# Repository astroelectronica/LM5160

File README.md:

# LM5160
Wide Input 65-V, 2-A Synchronous Buck / Fly-Buck DC/DC Converter

https://www.ti.com/product/LM5160

AE01007160

----

Small Footprint Isolated DC/DC Converter for Analog Input Module Reference Design

https://www.ti.com/tool/TIDA-00689

TIDA-00689

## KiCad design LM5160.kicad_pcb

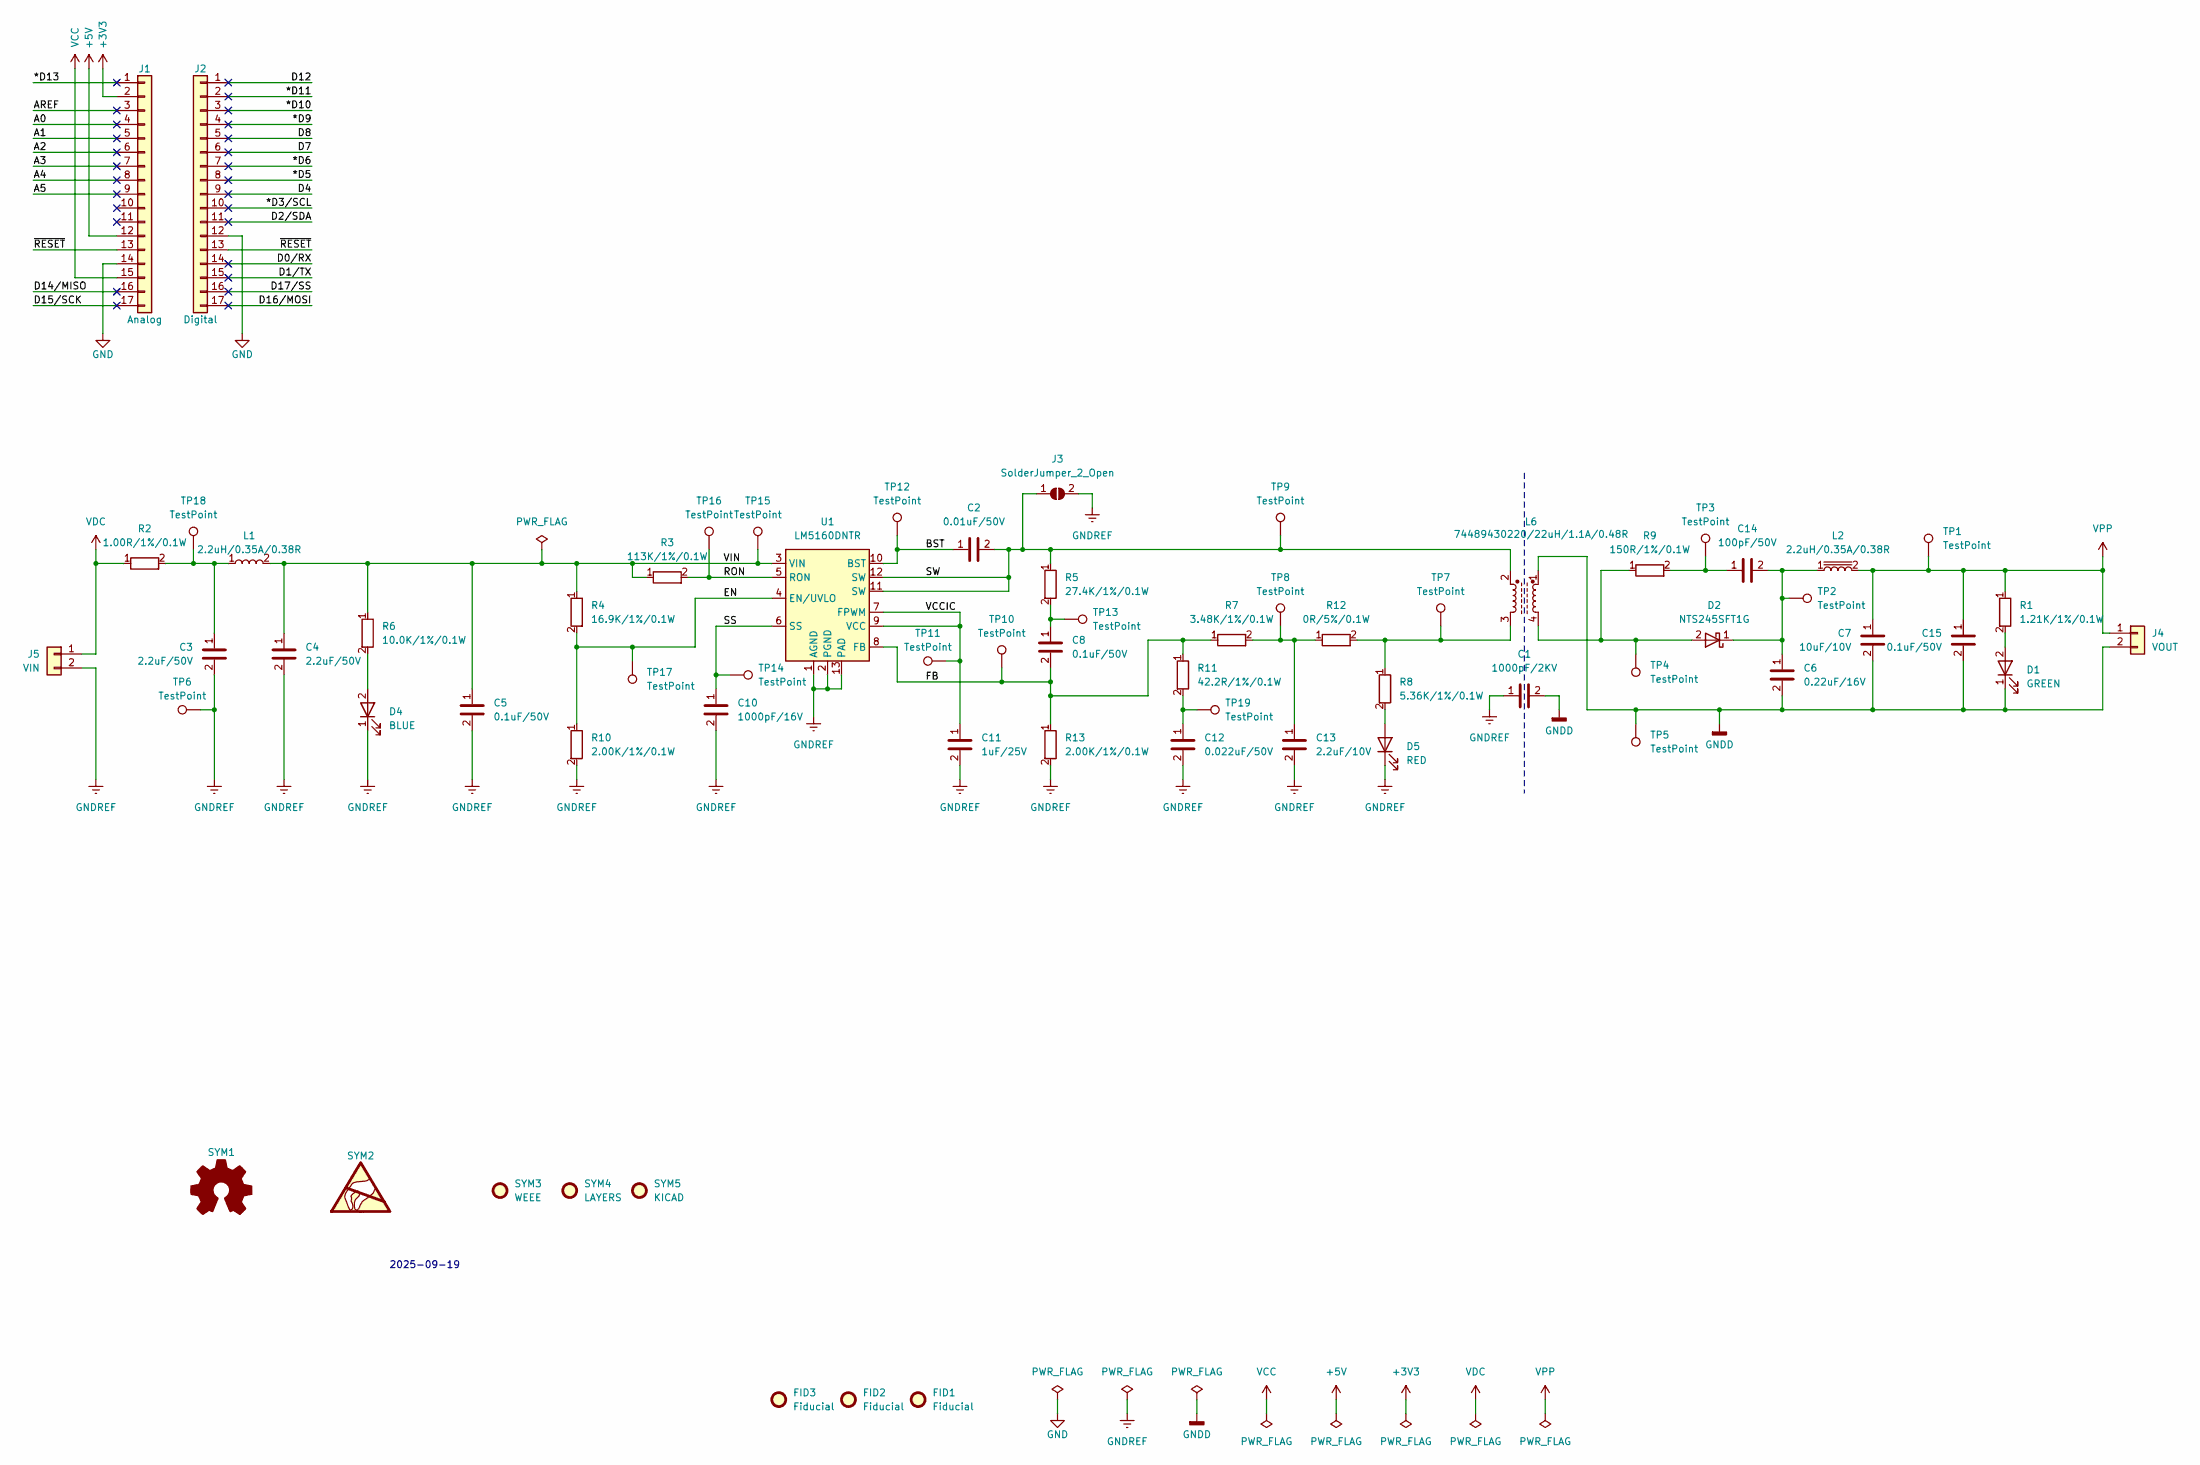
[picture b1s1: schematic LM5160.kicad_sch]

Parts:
C1: 1000pF/2KV; C_1206_3216Metric
C2: 0.01uF/50V; C_0603_1608Metric
C3, C4: 2.2uF/50V; C_1206_3216Metric
C5, C8, C15: 0.1uF/50V; C_0603_1608Metric
C6: 0.22uF/16V; C_0603_1608Metric
C7: 10uF/10V; C_0805_2012Metric
C10: 1000pF/16V; C_0603_1608Metric
C11: 1uF/25V; C_0603_1608Metric
C12: 0.022uF/50V; C_0603_1608Metric
C13: 2.2uF/10V; C_0603_1608Metric
C14: 100pF/50V; C_0603_1608Metric
D1: GREEN; LED_0603_1608Metric
D2: NTS245SFT1G; D_SOD-123F
D4: BLUE; LED_0603_1608Metric
D5: RED; LED_0603_1608Metric
FID1, FID2, FID3: Fiducial; Fiducial_0.75mm_Mask2.25mm
J1: Analog; PinHeader_1x17_P2.54mm_Vertical
J2: Digital; PinHeader_1x17_P2.54mm_Vertical
J3: SolderJumper_2_Open; SolderJumper-2_P1.3mm_Open_Pad1.0x1.5mm
J4: VOUT; PinHeader_1x02_P2.54mm_Vertical
J5: VIN; PinHeader_1x02_P2.54mm_Vertical
L1, L2: 2.2uH/0.35A/0.38R; L_0603_1608Metric
L6: 74489430220/22uH/1.1A/0.48R
R1: 1.21K/1%/0.1W; R_0603_1608Metric
R2: 1.00R/1%/0.1W; R_0603_1608Metric
R3: 113K/1%/0.1W; R_0603_1608Metric
R4: 16.9K/1%/0.1W; R_0603_1608Metric
R5: 27.4K/1%/0.1W; R_0603_1608Metric
R6: 10.0K/1%/0.1W; R_0603_1608Metric
R7: 3.48K/1%/0.1W; R_0603_1608Metric
R8: 5.36K/1%/0.1W; R_0603_1608Metric
R9: 150R/1%/0.1W; R_0603_1608Metric
R10, R13: 2.00K/1%/0.1W; R_0603_1608Metric
R11: 42.2R/1%/0.1W; R_0603_1608Metric
R12: 0R/5%/0.1W; R_0603_1608Metric
SYM1: Logo_Open_Hardware_Small; OSHW-Symbol_6.7x6mm_SilkScreen
SYM2: SYM_ESD_Large; ESD-Logo_6.6x6mm_SilkScreen
SYM3: WEEE; WEEE-Logo_4.2x6mm_SilkScreen
SYM4: LAYERS; LayerMarker_4_6.35x2.54mm_TextH1mm_P1.27mm_BottomMirrored
SYM5: KICAD; KiCad-Logo2_5mm_SilkScreen
TP1, TP2, TP3, TP4, TP5, TP6, TP7, TP8, TP9, TP10, TP11, TP12, TP13, TP14, TP15, TP16, TP17, TP18, TP19: TestPoint; TestPoint_Pad_D1.0mm
U1: LM5160DNTR; WSON-12-1EP_4x4mm_P0.5mm_EP2.6x3mm_ThermalVias

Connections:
+3V3: J1.2
+5V: J1.12
/*D3/SCL: J2.10
/*D5: J2.8
/*D6: J2.7
/*D9: J2.4
/*D10: J2.3
/*D11: J2.2
/*D13: J1.1
/A0: J1.4
/A1: J1.5
/A2: J1.6
/A3: J1.7
/A4: J1.8
/A5: J1.9
/AREF: J1.3
/BST: C2.1, TP12.1, U1.10 (BST)
/D0/RX: J2.14
/D1/TX: J2.15
/D2/SDA: J2.11
/D4: J2.9
/D7: J2.6
/D8: J2.5
/D12: J2.1
/D14/MISO: J1.16
/D15/SCK: J1.17
/D16/MOSI: J2.17
/D17/SS: J2.16
/EN: R4.2, R10.1, TP17.1, U1.4 (EN/UVLO)
/FB: C8.2, R7.1, R11.1, R13.1, TP10.1, U1.8 (FB)
/RON: R3.2, TP16.1, U1.5 (RON)
/SS: C10.1, TP14.1, U1.6 (SS)
/SW: C2.2, J3.1 (A), L6.2, R5.1, TP9.1, U1.11 (SW), U1.12 (SW)
/VCCIC: C11.1, TP11.1, U1.7 (FPWM), U1.9 (VCC)
/VIN: C4.1, C5.1, L1.2, R3.1, R4.1, R6.1, TP15.1, U1.3 (VIN)
/~RESET: J1.13, J2.13
GND: J1.14, J2.12
GNDD: C1.2, C6.2, C7.2, C15.2, D1.1 (K), J4.2, L6.1, TP5.1
GNDREF: C1.1, C3.2, C4.2, C5.2, C10.2, C11.2, C12.2, C13.2, D4.1 (K), D5.1 (K), J3.2 (B), J5.2, R10.2, R13.2, TP6.1, U1.1 (AGND), U1.2 (PGND), U1.13 (PAD)
unnamed: C3.1, L1.1, R2.2, TP18.1
unnamed: C8.1, R5.2, TP13.1
unnamed: C12.1, R11.2, TP19.1
unnamed: C13.1, R7.2, R12.1, TP8.1
unnamed: C14.1, R9.2, TP3.1
unnamed: D1.2 (A), R1.2
unnamed: D2.2 (A), L6.4, R9.1, TP4.1
unnamed: C6.1, C14.2, D2.1 (K), L2.1, TP2.1
unnamed: D4.2 (A), R6.2
unnamed: D5.2 (A), R8.2
unnamed: L6.3, R8.1, R12.2, TP7.1
VCC: J1.15
VDC: J5.1, R2.1
VPP: C7.1, C15.1, J4.1, L2.2, R1.1, TP1.1

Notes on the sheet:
${ISSUE_DATE}

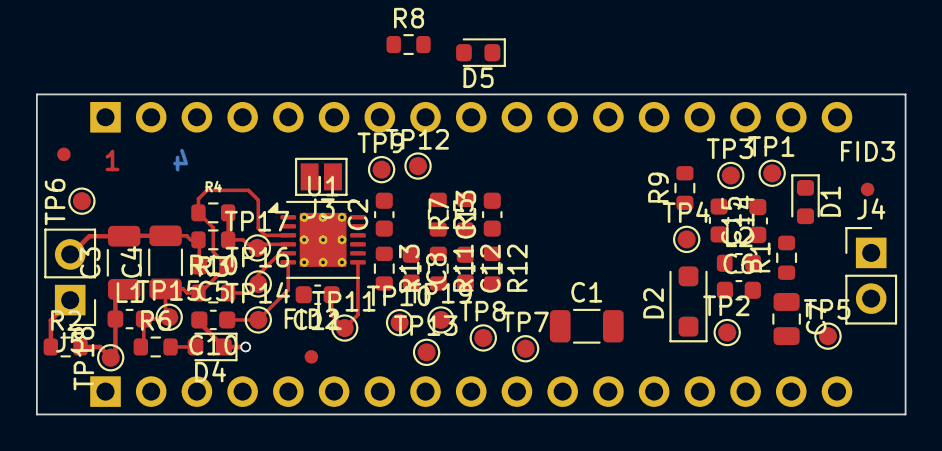
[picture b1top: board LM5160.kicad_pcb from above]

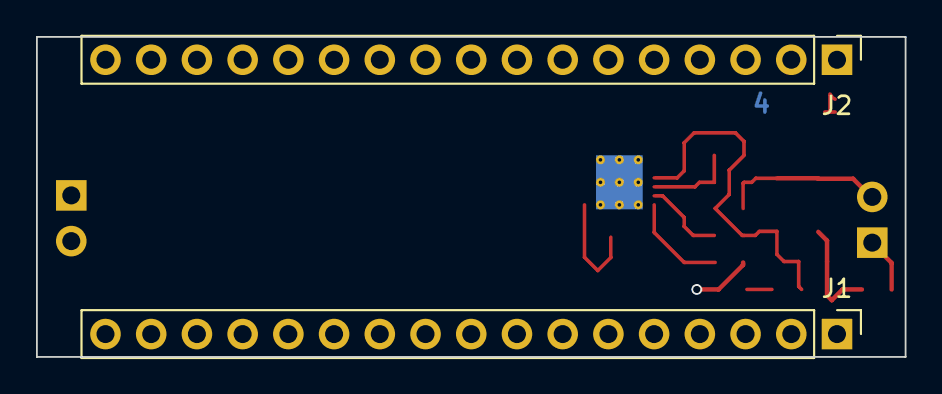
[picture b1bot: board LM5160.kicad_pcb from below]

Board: 4 copper layers, 48.3 x 17.8 mm, 70 parts (6 on the bottom side), 25 nets.

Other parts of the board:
MH1, MH2, MH3, MH4: MountingHole_1.2mm
